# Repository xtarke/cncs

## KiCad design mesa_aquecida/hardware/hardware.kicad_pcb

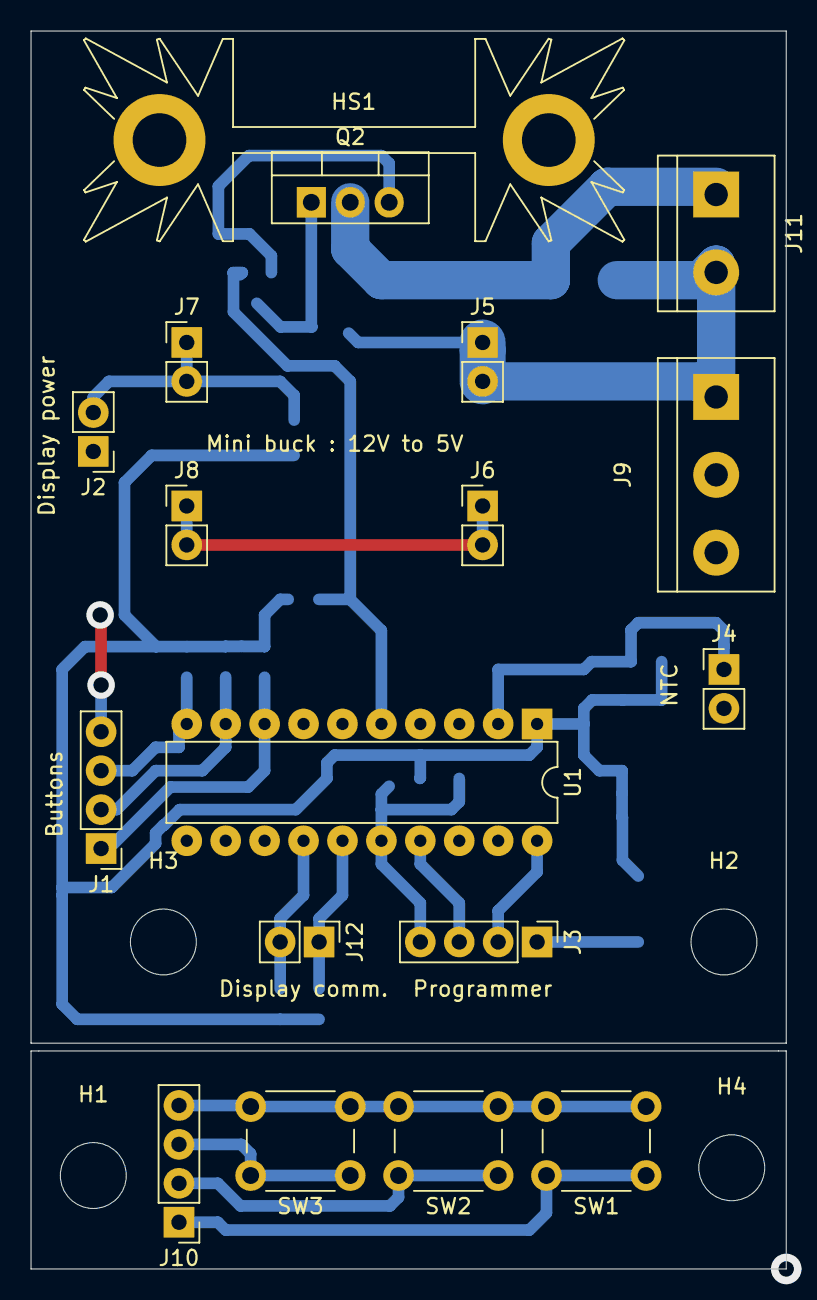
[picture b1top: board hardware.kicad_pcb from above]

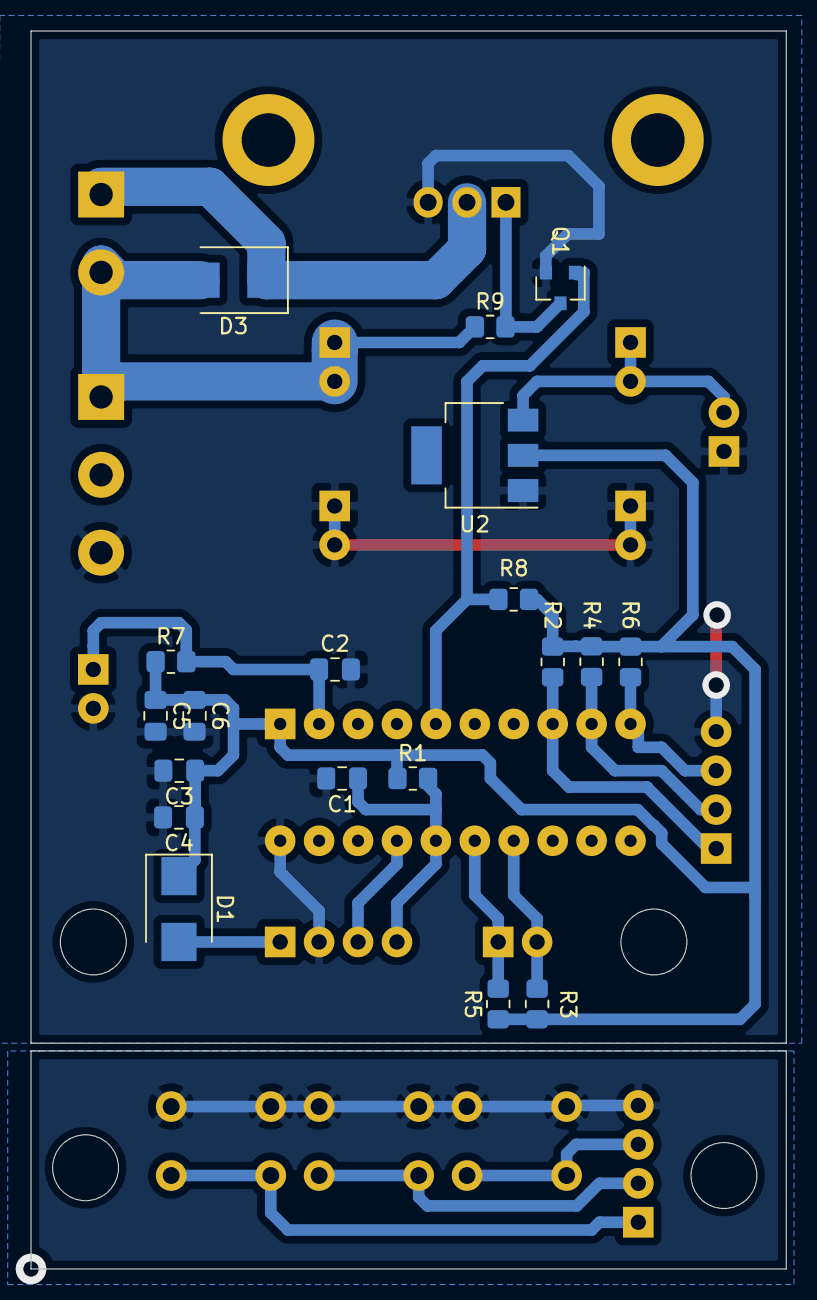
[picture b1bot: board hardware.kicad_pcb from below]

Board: 2 copper layers, 49.3 x 80.8 mm, 41 parts (19 on the bottom side), 20 nets.

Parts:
C1: 1n; C_0805_2012Metric_Pad1.18x1.45mm_HandSolder
C2, C4, C6: 100n; C_0805_2012Metric_Pad1.18x1.45mm_HandSolder
C3, C5: 10u; C_0805_2012Metric_Pad1.18x1.45mm_HandSolder
D1: D_Schottky; D_SMB
D3: DIODE; D_SMB
H1, H2, H3, H4: MountingHole; MountingHole_4.3mm_M4
HS1: Heatsink; Heatsink_Fischer_SK104-STCB_35x13mm__2xDrill3.5mm_ScrewM3
J1, J3, J10: Conn_01x04_Male; PinHeader_1x04_P2.54mm_Vertical
J2, J4, J12: Conn_01x02_Female; PinHeader_1x02_P2.54mm_Vertical
J5, J6, J7, J8: Conn_01x02_Male; PinHeader_1x02_P2.54mm_Vertical
J9: Screw_Terminal_01x03; TerminalBlock_bornier-3_P5.08mm
J11: Screw_Terminal_01x02; TerminalBlock_bornier-2_P5.08mm
Q1: 2N7002; SOT-23
Q2: IRF540N; TO-220-3_Vertical
R1: 47K; R_0805_2012Metric_Pad1.20x1.40mm_HandSolder
R2, R3, R4, R5, R6: 2k2; R_0805_2012Metric_Pad1.20x1.40mm_HandSolder
R7: 82k; R_0805_2012Metric_Pad1.20x1.40mm_HandSolder
R8: 500R; R_0805_2012Metric_Pad1.20x1.40mm_HandSolder
R9: 10k; R_0805_2012Metric_Pad1.20x1.40mm_HandSolder
SW1, SW2, SW3: SW_MEC_5E; SW_PUSH_6mm
U1: MSP430G2452IN20; DIP-20_W7.62mm
U2: NCP1117-3.3_SOT223; SOT-223-3_TabPin2

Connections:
+3V3: C3.1, C4.1, C5.1, C6.1, D1.1, R1.1, R2.1, R3.1, R4.1, R5.1, R6.1, R7.1, R8.1, U1.1, U2.2
+5V: J2.2, J7.1, J7.2, U2.3
+12V: D3.2, J5.1, J5.2, J9.1, J11.2, R9.1
GND: C1.2, C2.2, C3.2, C4.2, C5.2, C6.2, J1.4, J2.1, J3.2, J4.2, J6.1, J6.2, J8.1, J8.2, J9.3, Q1.2, Q2.3, U1.20, U2.1
GND1: J10.4, SW1.2, SW2.2, SW3.2
NTC: C2.1, J4.1, R7.2, U1.2
unnamed: D1.2, J3.1
unnamed: D3.1, J11.1, Q2.2
unnamed: J1.1, R2.2, U1.8
unnamed: J1.2, R4.2, U1.9
unnamed: J1.3, R6.2, U1.10
unnamed: J10.1, SW1.1
unnamed: J10.2, SW2.1
unnamed: J10.3, SW3.1
unnamed: Q1.3, Q2.1, R9.2
POWER: Q1.1, R8.2, U1.5
RST: C1.1, J3.4, R1.2, U1.16
SBWTCK: J3.3, U1.17
SCL: J12.2, R3.2, U1.14
SDA: J12.1, R5.2, U1.15

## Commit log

2020-12-08 Added files
2021-08-09 Added msp code
2021-08-10 Implemented IHM and ADC/Filter
2021-08-12 Added hardware
2021-08-13 updated schematic, removed diodes
2021-08-13 Updated PCB
2021-08-16 Created pcb
2021-08-17 Added aligment hole
2021-08-18 Adicionado corte
2021-08-19 Criado case
2021-08-23 Added ntc table
2021-08-24 Updated software
2021-08-27 Added ntc (open) protection. Remove delay in min loop
2021-11-16 Added camera support
2021-11-17 Added 3d files
2021-11-18 Added clamps
2021-11-19 Added new flat clamp
2021-11-22 Added stl files
2021-11-23 Added hole in flat clamp
2021-11-29 Added long clamp
2022-02-17 Added par box
2022-02-17 Added param. box cover
2022-02-18 Finished spinner box
2022-04-04 Added box and new corner conn
